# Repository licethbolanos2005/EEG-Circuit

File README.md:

# Implementación de un Electroencefalógrafo para Síntesis Musical

Este proyecto se centra en el diseño de un electroencefalograma (EEG) con énfasis en interfaz cerebro-computadora (BCI). Su objetivo es proporcionar a personas con discapacidad motora una herramienta adicional de interacción mediante un aplicativo de computadora que recopila señales cerebrales a través de electrodos ubicados en una bandana.

## Estructura del repositorio

Este repositorio contiene las siguientes carpetas:

- **Schematic**: Contiene las diferentes versiones del esquemático del proyecto, diseñadas con AutoDesk Eagle. Cada versión refleja el proceso de desarrollo y los cambios implementados con el tiempo.
- **libraries**: Incluye todas las librerías utilizadas para la creación del esquemático.
- **Board**: Contiene las diferentes versiones de los diseños de la placa desarrollados para el proyecto, reflejando las modificaciones y mejoras a lo largo del tiempo.

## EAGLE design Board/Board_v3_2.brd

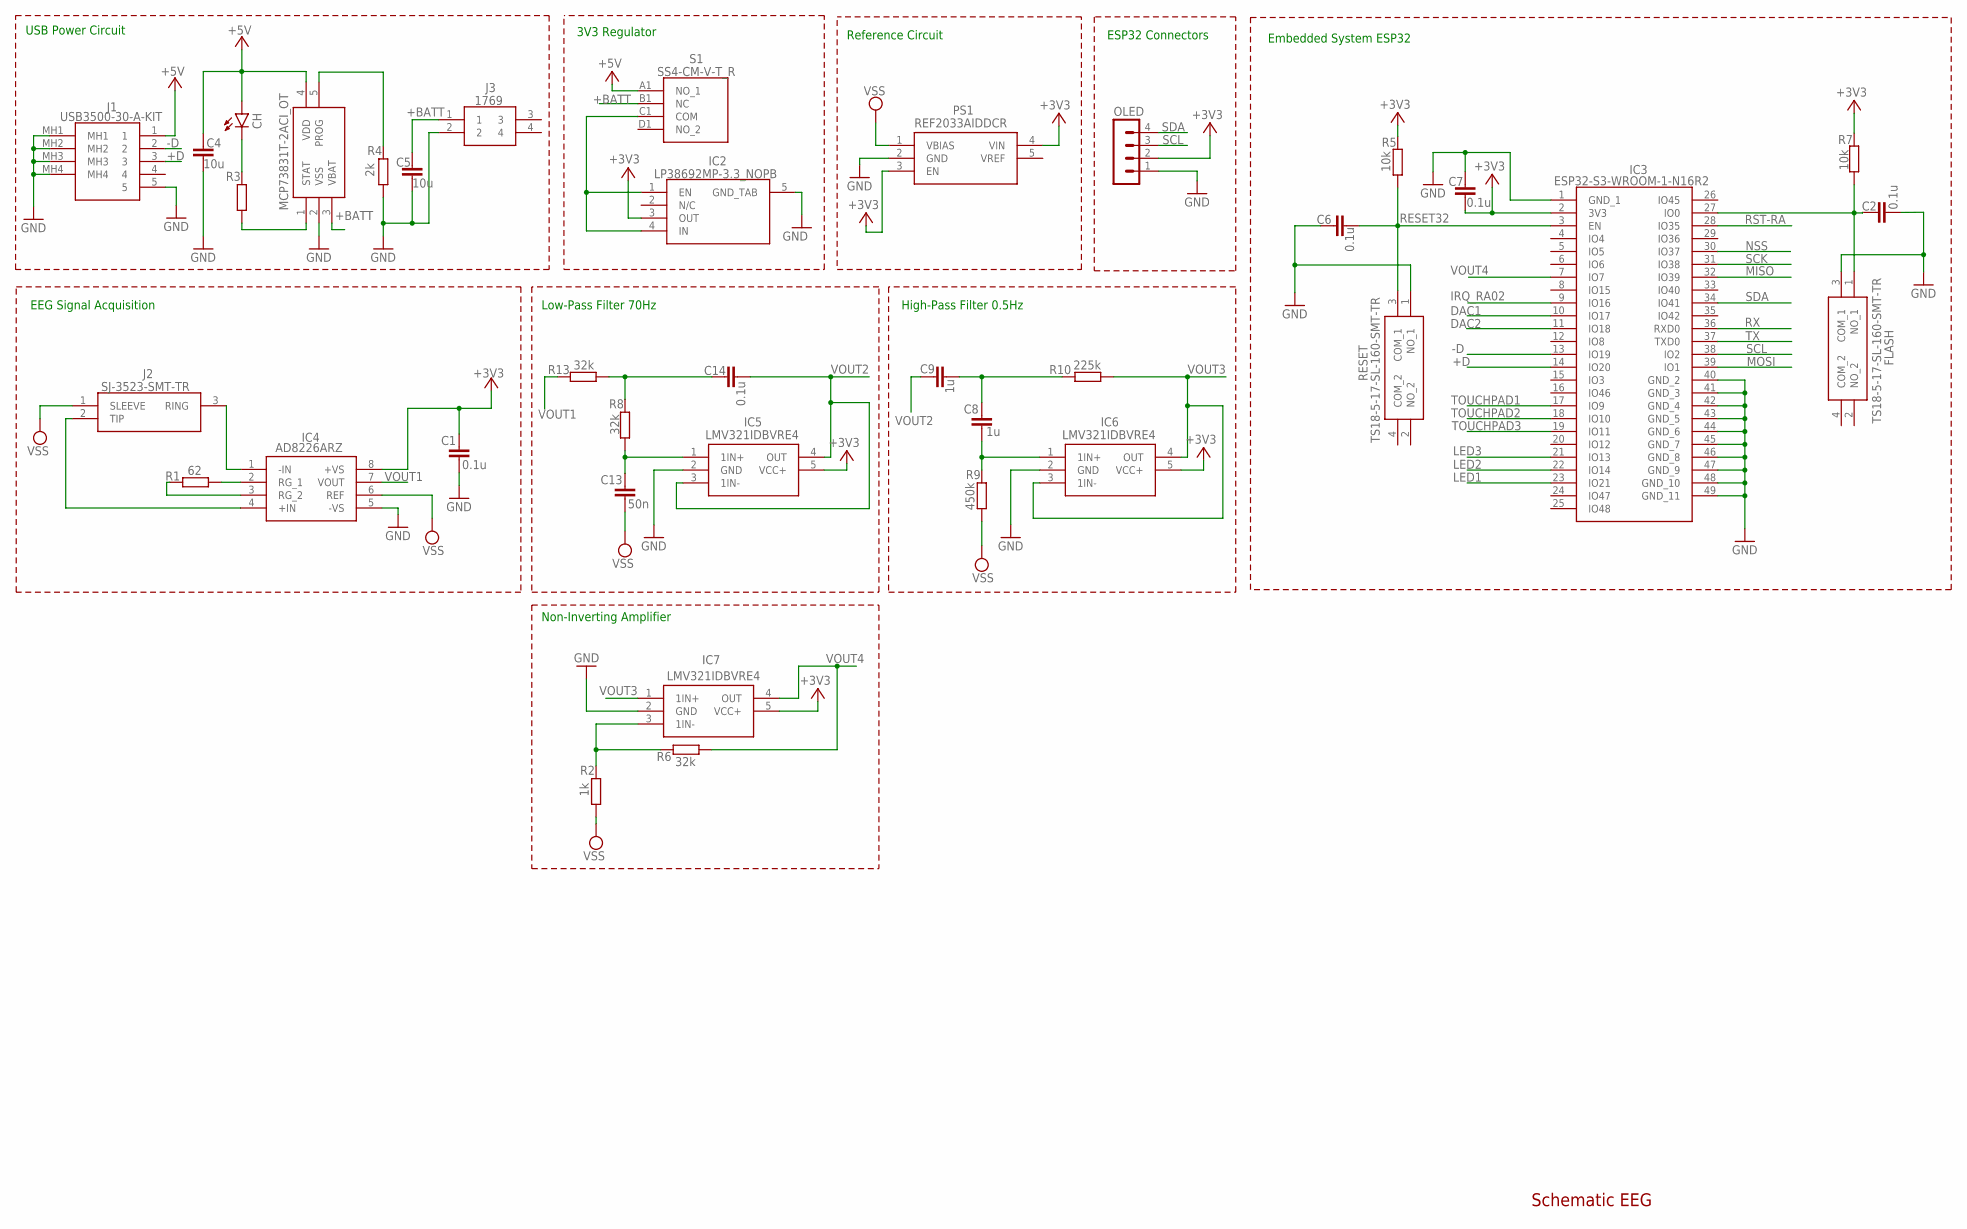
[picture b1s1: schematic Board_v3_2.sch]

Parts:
C1, C2, C6, C7, C14: 0.1u; C0805
C4, C5: 10u; C0805
C8, C9: 1u; C0805
C13: 50n; C0805
CH: LEDCHIP-LED0805; CHIP-LED0805
FLASH: TS18-5-17-SL-160-SMT-TR; TS18517SL160SMTTR
IC1: MCP73831T-2ACI_OT; SOT95P270X145-5N
IC2: LP38692MP-3.3_NOPB; SOT150P700X180-5N
IC3: ESP32-S3-WROOM-1-N16R2; ESP32S3WROOM1N16R2
IC4: AD8226ARZ; SOIC127P600X175-8N
IC5, IC6, IC7: LMV321IDBVRE4; SOT95P280X145-5N
J1: USB3500-30-A-KIT; USB350030AKIT
J2: SJ-3523-SMT-TR; SJ3523SMTTR
J3: 1769
OLED: MA04-1
PS1: REF2033AIDDCR; SOT95P280X110-5N
R1: 62; R0805
R2: 1k; R0805
R3: 220; R0805
R4: 2k; R0805
R5, R7: 10k; R0805
R6, R8, R13: 32k; R0805
R9: 450k; R0805
R10: 225k; R0805
RESET: TS18-5-17-SL-160-SMT-TR; TS18517SL160SMTTR
S1: SS4-CM-V-T_R; SS4CMVTR

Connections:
+3V3: C1.1, C7.2, IC2.3 (OUT), IC3.2 (3V3), IC4.8 (+VS), IC5.5 (VCC+), IC6.5 (VCC+), IC7.5 (VCC+), OLED.2, PS1.3 (EN), PS1.4 (VIN), R5.2, R7.2
+5V: C4.2, CH.A, IC1.4 (VDD), J1.1, S1.A1 (NO_1)
+BATT: C5.2, IC1.3 (VBAT), J3.1, S1.B1 (NC)
+D: IC3.14 (IO20), J1.3
-D: IC3.13 (IO19), J1.2
DAC1: IC3.10 (IO17)
DAC2: IC3.11 (IO18)
GND: C1.2, C2.2, C4.1, C5.1, C6.1, C7.1, FLASH.3 (COM_1), IC1.2 (VSS), IC2.5 (GND_TAB), IC3.1 (GND_1), IC3.40 (GND_2), IC3.41 (GND_3), IC3.42 (GND_4), IC3.43 (GND_5), IC3.44 (GND_6), IC3.45 (GND_7), IC3.46 (GND_8), IC3.47 (GND_9), IC3.48 (GND_10), IC3.49 (GND_11), IC4.5 (-VS), IC5.2 (GND), IC6.2 (GND), IC7.2 (GND), J1.5, J1.MH1, J1.MH2, J1.MH3, J1.MH4, J3.2, OLED.1, PS1.2 (GND), R4.1, RESET.1 (NO_1)
IRQ_RA02: IC3.9 (IO16)
LED1: IC3.23 (IO21)
LED2: IC3.22 (IO14)
LED3: IC3.21 (IO13)
MISO: IC3.32 (IO39)
MOSI: IC3.39 (IO1)
unnamed: IC4.2 (RG_1), R1.2
unnamed: IC4.3 (RG_2), R1.1
unnamed: IC4.1 (-IN), J2.3 (RING)
unnamed: IC4.4 (+IN), J2.2 (TIP)
unnamed: C8.2, IC6.1 (1IN+), R9.2
unnamed: IC1.1 (STAT), R3.1
unnamed: IC1.5 (PROG), R4.2
unnamed: CH.C, R3.2
unnamed: C8.1, C9.2, R10.1
unnamed: C2.1, FLASH.1 (NO_1), IC3.27 (IO0), R7.1
unnamed: C13.1, IC5.1 (1IN+), R8.1
unnamed: IC2.1 (EN), IC2.4 (IN), S1.C1 (COM)
unnamed: IC7.3 (1IN-), R2.2, R6.2
unnamed: C14.1, R8.2, R13.2
NSS: IC3.30 (IO37)
RESET32: C6.2, IC3.3 (EN), R5.1, RESET.3 (COM_1)
RST-RA: IC3.28 (IO35)
RX: IC3.36 (RXD0)
SCK: IC3.31 (IO38)
SCL: IC3.38 (IO2), OLED.3
SDA: IC3.34 (IO41), OLED.4
TOUCHPAD1: IC3.17 (IO9)
TOUCHPAD2: IC3.18 (IO10)
TOUCHPAD3: IC3.19 (IO11)
TX: IC3.37 (TXD0)
VOUT1: IC4.7 (VOUT), R13.1
VOUT2: C9.1, C14.2, IC5.3 (1IN-), IC5.4 (OUT)
VOUT3: IC6.3 (1IN-), IC6.4 (OUT), IC7.1 (1IN+), R10.2
VOUT4: IC3.7 (IO7), IC7.4 (OUT), R6.1
VSS: C13.2, IC4.6 (REF), J2.1 (SLEEVE), PS1.1 (VBIAS), R2.1, R9.1

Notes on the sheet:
Schematic EEG
USB Power Circuit
3V3 Regulator
Reference Circuit
Embedded System ESP32
ESP32 Connectors
Low-Pass Filter 70Hz
High-Pass Filter 0.5Hz
EEG Signal Acquisition
Non-Inverting Amplifier

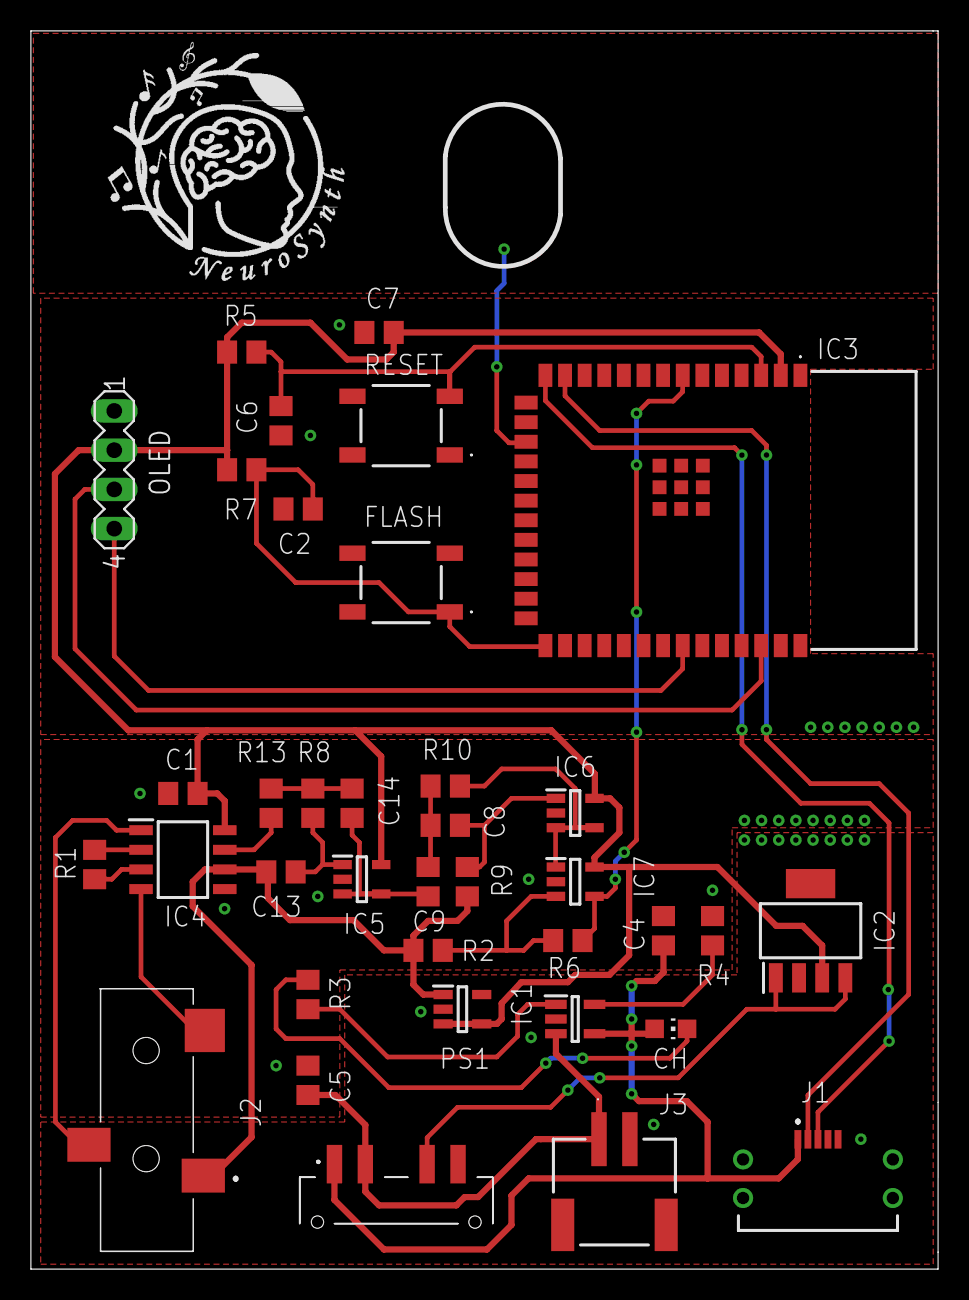
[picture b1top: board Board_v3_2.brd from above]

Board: 2 copper layers, 58.7 x 80.2 mm, 37 parts (0 on the bottom side), 28 nets.

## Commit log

2025-03-23 El primer diseño de esquemático realizado por todos, con las correcciones del docente
2025-03-24 Se Agregro el bloque de carga de batería
2025-03-24 Agregué librerías usadas en el primer esquemático
2025-03-24 Primer esquemático realizado por todos
2025-03-24 Agregué librerías usadas en Schematic_v1_0.sch
2025-03-24 Agregué el bloque de carga de batería
2025-03-24 Agregué las librerías usadas en Schematic_v2_0.sch
2025-03-24 Agregué las librerías usadas en Schematic_v2_1
2025-03-24 Agregué el bloque de sistemas embebido
2025-03-25 READ ME
2025-03-25 Librería del OPA317IDR
2025-03-27 Librería Regulador de Voltaje
2025-03-27 Librería Voltaje de Referencia (Tierra Común)
2025-03-27 Agregué las librerías usadas en Schematic_v2_2.sch
2025-03-27 Agregue los bloques: Regulador 3V3 y Voltaje Referencia
    Así mismo realicé correcciones en la visualización de los bloques y conexiones de los bloques pasados.
2025-03-28 Agregué las librerías usadas en Schematic_v2_3.sch
2025-03-28 Agregué Los bloques: Conectores de ESP32 y Filtros
2025-03-29 Agregué la librería usada en Schematic_v3_0.sch
2025-03-29 Corregí los bloques de Regulador 3v3 y Voltaje Referencia
2025-03-29 Agregué las librerías usadas en Schematic_v3_1.sch
2025-03-29 Add files via upload
    Corregí los bloques de Adquisición de señales, Conectores de ESP32 y Filtros
2025-03-29 Corregí los bloques de Adquisición de señales, Conectores de ESP32 Y Filtros
2025-03-29 Corregí el bloque de carga de batería
2025-03-30 correji el bloque de sistema embebido
2025-03-30 agregue libreria usadas en Schematic_v3_3.sch
2025-03-30 Corregí el bloque del sistema Embebido
2025-03-30 Agregue librería usada en Schematic_v3_3.sch
2025-03-30 Corregi el bloque de carga de batería
2025-03-30 Agregué librería usada en Schematic_v3_2.sch
2025-04-04 Primer Diseño de PCB realizado
2025-04-05 Agregué el bloque de amplificador no inversor
2025-04-05 Primer diseño de la pcb
2025-04-05 Esquemático del proyecto
2025-04-05 Realicé el montaje de los componentes electrónicos en la PCB
2025-04-06 Corregí el orden de los componentes y realicé pistas entre los componentes
2025-04-06 Corregí el orden de los componentes y realicé pistas entre los componentes
2025-04-06 Corregí tamaño de pistas y agregué las faltantes.
2025-04-08 Corregí tamaño y ángulos rectos en las pistas, y cambié la organización de algunos componentes
2025-04-11 Correcciones del profesor
2025-04-22 Realicé los planos de tierra y corregí algunas conexiones
2025-04-23 Agregué el touchpad y corregí algunas conexiones
2025-04-24 Agregué el logo al diseño
2025-04-25 Realicé revisión del diseño
2025-04-25 Realicé revisión del diseño y deshabilité algunas capas
2025-04-25 Reemplacé la ESP32 por una que se encuentra disponible
2025-04-25 Agregué la librería de la ESP32 que se encuentra disponible
2025-04-25 Agregué los valores de los componentes
2025-05-05 Organicé los nombres de los componentes y corregí conexión en el esquemático
2025-05-05 Realicé una pista de una conexión faltante
2025-05-06 Agregué un pad de tierra en una isla huérfana
